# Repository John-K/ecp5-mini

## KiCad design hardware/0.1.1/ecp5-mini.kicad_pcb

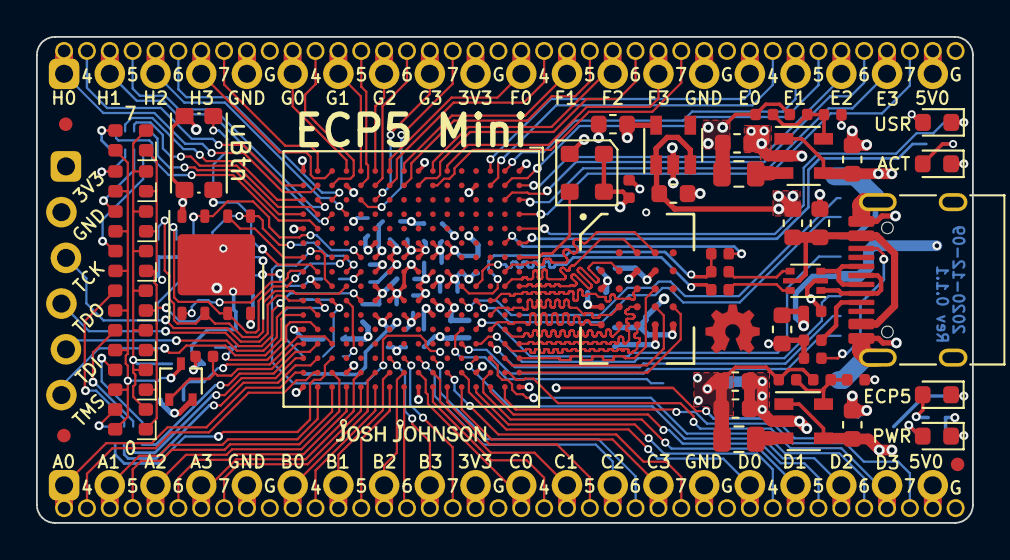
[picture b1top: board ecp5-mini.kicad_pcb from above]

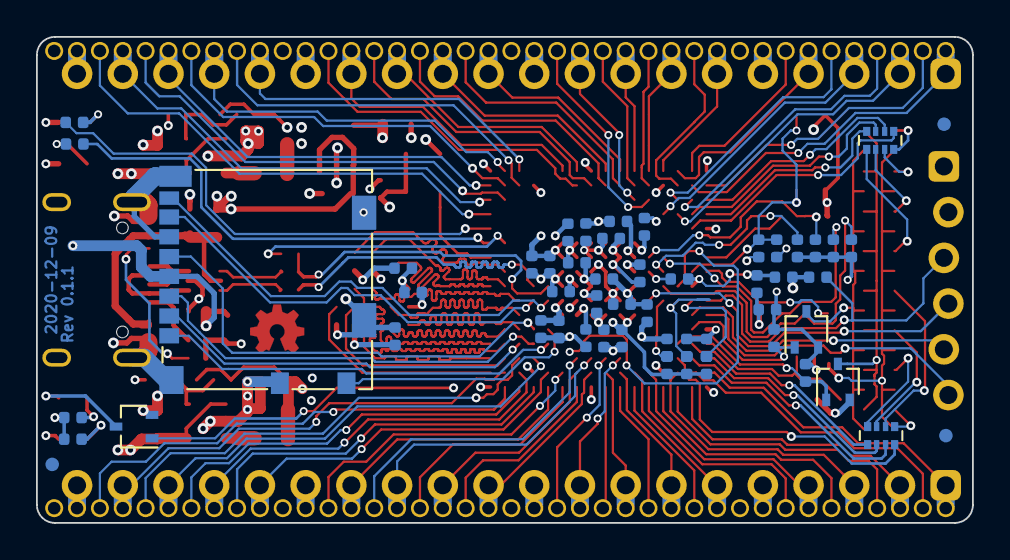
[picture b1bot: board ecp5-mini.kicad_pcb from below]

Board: 4 copper layers, 52.0 x 27.0 mm, 111 parts (55 on the bottom side), 149 nets.

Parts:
C1, C2, C6: 4u7; C_0603_1608Metric
C3, C4: 1u; C_0603_1608Metric
C5, C11: 10u; C_0603_1608Metric
C7, C10: 22u; C_0603_1608Metric
C8, C9: 6p8; C_0402_1005Metric
C12, C13, C14, C15, C17, C18, C19, C20, C25, C26, C31, C32, C37, C38, C39, C40, C41, C42, C43, C45, C46, C47: 100n; C_0402_1005Metric
C21, C22, C23, C29, C30: 4u7; C_0402_1005Metric
D1, D2, D3, D12: PINK; LED_0603_1608Metric
D4, D5, D6, D7, D8, D9, D10, D11: 2020RGBA; LED_TRI_2020
F1: 1A; Fuse_0603_1608Metric
FID1, FID2, FID3, FID4, FID5, FID6: Fiducial; Fiducial_0.75mm_Mask1.5mm
J1: Micro_SD_Card; microSD_HC_Molex_104031-0811
J2: JTAG; STM_6_PIN_THT_Staggered
J3, J4: S7 Mini; ECP5-Mini-Edge-20x2.54-40x1.27
J5: USB_C_Receptacle_USB2.0; USB_C_Receptacle_HRO_TYPE-C-31-M-12
L1, L2: 2u2; L_0805_2012Metric
LOGO1: Josh-Logo; josh-johnson-logo-8_6x1_5
LOGO2: OSHW_FMask; OSHW_Logo_3.6x3.6_F.Mask
Q1, Q2, Q3, Q4: BSS138; SOT-323_SC-70
R1: 210k; R_0402_1005Metric
R2: 47k; R_0402_1005Metric
R3: 84k5; R_0402_1005Metric
R4: 100k; R_0402_1005Metric
R5, R21, R22, R23: 2K2; R_0402_1005Metric
R6, R7, R12, R19: 5K1; R_0402_1005Metric
R8, R24, R25, R26, R27, R28, R29, R30: 10K; R_0402_1005Metric
R9, R10, R20: 22R; R_0402_1005Metric
R11, R13, R14, R15, R16, R17, R18: 1K5; R_0402_1005Metric
RN2, RN3: 220R; R_Array_Convex_4x0402
SW1: KMR2; SW_Push_KMR2
U1: ECP5U_12_CABGA256; BGA-256_14.0x14.0mm_Layout16x16_P0.8mm_Ball0.45mm_Pad0.32mm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
U2: TLV73325PDBV; SOT-23-5
U3, U5: TLV62568DBV; SOT-23-5
U4: USBLC6-2P6; SOT-666
U6: W25Q128JVPIQ; WSON-8-1EP_6x5mm_P1.27mm_EP3.4x4.3mm
U7: S27KL0641; BGA-24_5x5_6.0x8.0mm
X1: DSC6101CI2A-016; CDFN_3.2x2.5mm_XO

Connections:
+1V1: C7.1, C8.1, C10.1, C21.1, C22.1, C37.1, C39.1, C41.1, C42.1, C43.1, L2.2, R3.1, U1.G6 (VCC[6]), U1.G7 (VCC[6]), U1.G9 (VCC[6]), U1.L8 (VCC[6]), U1.L9 (VCC[6]), U1.L10 (VCC[6])
+2V5: C4.1, C38.1, C40.1, U1.G11 (VCCAUX[2]), U1.L7 (VCCAUX[2]), U2.5 (OUT)
+3V3: C5.1, C9.1, C11.1, C12.1, C14.1, C17.1, C18.1, C19.1, C20.1, C23.1, C25.1, C26.1, C29.1, C30.1, C31.1, C32.1, C45.1, C46.1, C47.1, J1.4 (VDD), J2.1, J3.19, J4.19, L1.2, R1.1, R5.1, R12.1, R13.1, R15.1, R17.1, R19.1, R21.2, R24.1, R26.1, R27.1, R29.1, U1.F6 (VCCIO0[2]), U1.F7 (VCCIO0[2]), U1.F10 (VCCIO1[2]), U1.F11 (VCCIO1[2]), U1.H6 (VCCIO7[2]), U1.H7 (VCCIO7[2]), U1.H11 (VCCIO2[2]), U1.J6 (VCCIO6[2]), U1.J7 (VCCIO6[2]), U1.J11 (VCCIO2[2]), U1.K11 (VCCIO3[2]), U1.L6 (VCCIO8), U1.L11 (VCCIO3[2]), U6.8 (VCC), U7.B4 (VCC), U7.D1 (VCCQ), U7.E4 (VCCQ), X1.1 (OE/STBY), X1.4 (VDD)
+5V: C1.1, C2.1, C3.1, F1.2, J3.39, J4.39, U2.1 (IN), U2.3 (EN), U3.1 (EN), U3.4 (VIN), U5.1 (EN), U5.4 (VIN)
/CLK_16MHZ: U1.A7 (PT29A/+/PCLKT0_0), X1.3 (OUT)
/FPGA Config/CFG_0: R13.2, R14.1, U1.N10 (CFG_0)
/FPGA Config/CFG_1: R15.2, R16.1, U1.P10 (CFG_1)
/FPGA Config/CFG_2: R17.2, R18.1, U1.R10 (CFG_2)
/FPGA Config/CFG_CDONE: Q1.1 (G), U1.P9 (DONE)
/FPGA Config/CFG_CLK: R27.2, U1.N9 (CCLK/MCLK/SCK), U6.6 (CLK)
/FPGA Config/CFG_CS: R29.2, U1.N8 (PB15A/+/HOLDN/DI/BUSY/CSSPIN/CEN), U6.1 (~CS)
/FPGA Config/CFG_IO0: U1.T8 (PB11B/-/D0/MOSI/IO0), U6.5 (DI(IO0))
/FPGA Config/CFG_IO1: U1.T7 (PB11A/+/D1/MISO/IO1), U6.2 (DO(IO1))
/FPGA Config/CFG_IO2: R26.2, U1.M7 (PB9B/-/D2/IO2), U6.3 (IO2)
/FPGA Config/CFG_IO3: R24.2, U1.N7 (PB9A/+/D3/IO3), U6.7 (IO3)
/FPGA Config/TCK: J2.3, R8.1, U1.T10 (TCK)
/FPGA Config/TDI: J2.5, U1.R11 (TDI)
/FPGA Config/TDO: J2.4, U1.M10 (TDO)
/FPGA Config/TMS: J2.6, U1.T11 (TMS)
/FPGA Config/nBTN_USR: C13.1, R12.2, SW1.2, U1.R8 (PB13A/+/SN/CSN)
/FPGA Config/nFPGA_RST: C15.1, R19.2, R20.1, U1.R9 (PROGRAMN)
/HR_CK: U1.A9 (PT42A/+), U7.B2 (CK)
/HR_DQ0: U1.A13 (PT65A/+), U7.D3 (DQ0)
/HR_DQ1: U1.C11 (PT49B/-), U7.D2 (DQ1)
/HR_DQ2: U1.A14 (PT65B/-), U7.C4 (DQ2)
/HR_DQ3: U1.B14 (PT67A/+), U7.D4 (DQ3)
/HR_DQ4: U1.A15 (PT67B/-), U7.D5 (DQ4)
/HR_DQ5: U1.B13 (PT60A/+), U7.E3 (DQ5)
/HR_DQ6: U1.B12 (PT56A/+), U7.E2 (DQ6)
/HR_DQ7: U1.C12 (PT56B/-), U7.E1 (DQ7)
/HR_RWDS: U1.C10 (PT44B/-), U7.C3 (RWDS)
/HR_nCS: U1.B9 (PT38A/+/GR_PCLK1_0), U7.A3 (~CS)
/HR_nRST: U1.B8 (PT35B/-/PCLKC1_0), U7.A4 (~RESET)
/LED_0: RN2.8, U1.P14 (PR38B/-/HS/RDQ44)
/LED_1: RN2.5, U1.R13 (PR41C/+/RDQ44)
/LED_2: RN2.6, U1.T14 (PR41D/-/RDQ44)
/LED_3: RN2.7, U1.R14 (PR41B/-/HS/RDQ44)
/LED_4: RN3.8, U1.T4 (PL44B/-/HS/LDQSN44)
/LED_5: RN3.7, U1.R4 (PL41C/+/LDQ44)
/LED_6: RN3.6, U1.T3 (PL41D/-/LDQ44)
/LED_7: RN3.5, U1.R5 (PL44A/+/HS/LDQS44)
/LED_ACT: R23.1, U1.A6 (PT18B/-)
/LED_B: Q4.1 (G), R30.1, U1.T13 (PR44B/-/HS/RDQSN44)
/LED_G: Q3.1 (G), R28.1, U1.P13 (PR41A/+/HS/RDQ44)
/LED_R: Q2.1 (G), R25.1, U1.R12 (PR44A/+/HS/RDQS44)
/LED_USR: R22.1, U1.A5 (PT18A/+)
/LEDs/CAT_B: D4.2 (BK), D5.2 (BK), D6.2 (BK), D7.2 (BK), D8.2 (BK), D9.2 (BK), D10.2 (BK), D11.2 (BK), Q4.3 (D)
/LEDs/CAT_G: D4.4 (GK), D5.4 (GK), D6.4 (GK), D7.4 (GK), D8.4 (GK), D9.4 (GK), D10.4 (GK), D11.4 (GK), Q3.3 (D)
/LEDs/CAT_R: D4.1 (RK), D5.1 (RK), D6.1 (RK), D7.1 (RK), D8.1 (RK), D9.1 (RK), D10.1 (RK), D11.1 (RK), Q2.3 (D)
/PORT_A0: J3.1, U1.T15 (PR38D/-/RDQ44)
/PORT_A1: J3.3, U1.R16 (PR35B/-/VREF1_3/HS/RDQ32)
/PORT_A2: J3.5, U1.P15 (PR32B/-/HS/RDQSN32)
/PORT_A3: J3.7, U1.M15 (PR26D/-/PCLKC3_0/RDQ32)
/PORT_A4: J3.2, U1.R15 (PR38C/+/RDQ44)
/PORT_A5: J3.4, U1.P16 (PR35A/+/HS/RDQ32)
/PORT_A6: J3.6, U1.N16 (PR32A/+/HS/RDQS32)
/PORT_A7: J3.8, U1.M16 (PR26C/+/PCLKT3_0/RDQ32)
/PORT_B0: J3.11, U1.L15 (PR26B/-/PCLKC3_1/HS/RDQ32)
/PORT_B1: J3.13, U1.K15 (PR23D/-/PCLKC2_0/RDQ20)
/PORT_B2: J3.15, U1.J15 (PR23B/-/PCLKC2_1/HS/RDQ20)
/PORT_B3: J3.17, U1.K14 (PR20D/-/RDQ20)
/PORT_B4: J3.12, U1.L16 (PR26A/+/PCLKT3_1/HS/RDQ32)
/PORT_B5: J3.14, U1.K16 (PR23C/+/PCLKT2_0/RDQ20)
/PORT_B6: J3.16, U1.J16 (PR23A/+/PCLKT2_1/HS/RDQ20)
/PORT_B7: J3.18, U1.J14 (PR20C/+/GR_PCLK2_0/RDQ20)
/PORT_C0: J3.21, U1.H15 (PR20B/-/HS/RDQSN20)
/PORT_C1: J3.23, U1.G15 (PR14B/-/HS/RDQ20)
/PORT_C2: J3.25, U1.H14 (PR14D/-/RDQ20)
/PORT_C3: J3.27, U1.E16 (PR11D/-/RDQ8)
/PORT_C4: J3.22, U1.G16 (PR20A/+/GR_PCLK2_1/HS/RDQS20)
/PORT_C5: J3.24, U1.F16 (PR14A/+/HS/RDQ20)
/PORT_C6: J3.26, U1.G14 (PR14C/+/VREF1_2/RDQ20)
/PORT_C7: J3.28, U1.F15 (PR11C/+/RDQ8)
/PORT_D0: J3.31, U1.E15 (PR8B/-/HS/RDQSN8)
/PORT_D1: J3.33, U1.C15 (PR5B/-/HS/RDQ8)
/PORT_D2: J3.35, U1.D14 (PR2D/-/RDQ8)
/PORT_D3: J3.37, U1.B15 (PR2B/-/S0_IN/HS/RDQ8)
/PORT_D4: J3.32, U1.D16 (PR8A/+/HS/RDQS8)
/PORT_D5: J3.34, U1.C16 (PR5A/+/HS/RDQ8)
/PORT_D6: J3.36, U1.C14 (PR2C/+/RDQ8)
/PORT_D7: J3.38, U1.B16 (PR2A/+/HS/RDQ8)
/PORT_E0: J4.31, U1.C1 (PL5A/+/HS/LDQ8)
/PORT_E1: J4.33, U1.B1 (PL2A/+/HS/LDQ8)
/PORT_E2: J4.35, U1.A2 (PT4A/+)
/PORT_E3: J4.37, U1.A3 (PT6A/+)
/PORT_E4: J4.32, U1.C2 (PL5B/-/HS/LDQ8)
/PORT_E5: J4.34, U1.B2 (PL2B/-/HS/LDQ8)
/PORT_E6: J4.36, U1.B3 (PT4B/-)
/PORT_E7: J4.38, U1.A4 (PT6B/-)
/PORT_F0: J4.21, U1.K1 (PL23C/+/PCLKT7_0/LDQ20)
/PORT_F1: J4.23, U1.J1 (PL23A/+/PCLKT7_1/HS/LDQ20)
/PORT_F2: J4.25, U1.G1 (PL20A/+/GR_PCLK7_1/HS/LDQS20)
/PORT_F3: J4.27, U1.F1 (PL14A/+/HS/LDQ20)
/PORT_F4: J4.22, U1.K2 (PL23D/-/PCLKC7_0/LDQ20)
/PORT_F5: J4.24, U1.J2 (PL23B/-/PCLKC7_1/HS/LDQ20)
/PORT_F6: J4.26, U1.H2 (PL20B/-/HS/LDQSN20)
/PORT_F7: J4.28, U1.G2 (PL14B/-/HS/LDQ20)
/PORT_G0: J4.11, U1.N1 (PL32A/+/HS/LDQS32)
/PORT_G1: J4.13, U1.M1 (PL26C/+/PCLKT6_0/LDQ32)
/PORT_G2: J4.15, U1.L1 (PL26A/+/PCLKT6_1/HS/LDQ32)
/PORT_G3: J4.17, U1.L3 (PL32C/+/LDQ32)
/PORT_G4: J4.12, U1.P2 (PL32B/-/HS/LDQSN32)
/PORT_G5: J4.14, U1.M2 (PL26D/-/PCLKC6_0/LDQ32)
/PORT_G6: J4.16, U1.L2 (PL26B/-/PCLKC6_1/HS/LDQ32)
/PORT_G7: J4.18, U1.M3 (PL32D/-/LDQ32)
/PORT_H0: J4.1, U1.R2 (PL38C/+/LDQ44)
/PORT_H1: J4.3, U1.P4 (PL41A/+/HS/LDQ44)
/PORT_H2: J4.5, U1.N4 (PL38A/+/HS/LDQ44)
/PORT_H3: J4.7, U1.P1 (PL35A/+/HS/LDQ32)
/PORT_H4: J4.2, U1.T2 (PL38D/-/LDQ44)
/PORT_H5: J4.4, U1.R3 (PL41B/-/HS/LDQ44)
/PORT_H6: J4.6, U1.P3 (PL38B/-/HS/LDQ44)
/PORT_H7: J4.8, U1.R1 (PL35B/-/VREF1_6/HS/LDQ32)
/SD_CLK: J1.5 (CLK), U1.D12 (PT58A/+)
/SD_CMD: J1.3 (CMD), U1.D13 (PT62A/+)
/SD_DAT0: J1.7 (DAT0), U1.D10 (PT47A/+)
/SD_DAT1: J1.8 (DAT1), U1.E10 (PT47B/-)
/SD_DAT2: J1.1 (DAT2), U1.E13 (PT62B/-)
/SD_DAT3: J1.2 (DAT3/CD), U1.C13 (PT60B/-)
/SD_DET: J1.10 (DET_A), U1.E12 (PT58B/-)
/USB_D+: R10.1, R11.1, U1.E9 (PT40B/-)
/USB_D-: R9.2, U1.D9 (PT40A/+)
/USB_PU: R11.2, U1.B6 (PT22B/-)
GND: C1.2, C2.2, C3.2, C4.2, C5.2, C6.2, C7.2, C10.2, C11.2, C12.2, C13.2, C14.2, C15.2, C17.2, C18.2, C19.2, C20.2, C21.2, C22.2, C23.2, C25.2, C26.2, C29.2, C30.2, C31.2, C32.2, C37.2, C38.2, C39.2, C40.2, C41.2, C42.2, C43.2, C45.2, C46.2, C47.2, D1.1 (K), D3.1 (K), D12.1 (K), J1.6 (VSS), J1.9 (DET_B), J1.11 (SHIELD), J2.2, J3.9, J3.10, J3.20, J3.29, J3.30, J3.40, J4.9, J4.10, J4.20, J4.29, J4.30, J4.40, J5.A1 (GND), J5.A12 (GND), J5.B1 (GND), J5.B12 (GND), J5.S1 (SHIELD), Q1.2 (S), Q2.2 (S), Q3.2 (S), Q4.2 (S), R2.2, R4.2, R6.2, R7.2, R8.2, R14.2, R16.2, R18.2, R25.2, R28.2, R30.2, SW1.1, U1.A1 (GND[27]), U1.A16 (GND[27]), U1.D2 (GND[27]), U1.D15 (GND[27]), U1.F8 (GND[27]), U1.F9 (GND[27]), U1.G8 (GND[27]), U1.G10 (GND[27]), U1.H1 (GND[27]), U1.H8 (GND[27]), U1.H9 (GND[27]), U1.H10 (GND[27]), U1.H16 (GND[27]), U1.J8 (GND[27]), U1.J9 (GND[27]), U1.J10 (GND[27]), U1.K6 (GND[27]), U1.K7 (GND[27]), U1.K8 (GND[27]), U1.K9 (GND[27]), U1.K10 (GND[27]), U1.N2 (GND[27]), U1.N15 (GND[27]), U1.T1 (GND[27]), U1.T5 (GND[27]), U1.T12 (GND[27]), U1.T16 (GND[27]), U2.2 (GND), U3.2 (GND), U4.2 (GND), U5.2 (GND), U6.4 (GND), U6.9 (GND), U7.B3 (VSS), U7.C1 (VSSQ), U7.E5 (VSSQ), X1.2 (GND)
unnamed: C6.1, F1.1, J5.A4 (VBUS), J5.A9 (VBUS), J5.B4 (VBUS), J5.B9 (VBUS), U4.5 (VBUS)
unnamed: C8.2, R3.2, R4.1, U5.5 (FB)
unnamed: C9.2, R1.2, R2.1, U3.5 (FB)
unnamed: D1.2 (A), R5.2
unnamed: D2.1 (K), Q1.3 (D)
unnamed: D2.2 (A), R21.1
unnamed: D3.2 (A), R22.2
unnamed: D4.3 (A), RN2.1
unnamed: D5.3 (A), RN2.4
unnamed: D6.3 (A), RN2.3
unnamed: D7.3 (A), RN2.2
unnamed: D8.3 (A), RN3.1
unnamed: D9.3 (A), RN3.2
unnamed: D10.3 (A), RN3.3
unnamed: D11.3 (A), RN3.4
unnamed: D12.2 (A), R23.2
unnamed: J5.A5 (CC1), R6.1
unnamed: J5.A6 (D+), J5.B6 (D+), U4.3 (IO2)
unnamed: J5.A7 (D-), J5.B7 (D-), U4.1 (IO1)
unnamed: J5.B5 (CC2), R7.1
unnamed: L1.1, U3.3 (SW)
unnamed: L2.1, U5.3 (SW)
unnamed: R9.1, U4.6 (IO1)
unnamed: R10.2, U4.4 (IO2)
unnamed: R20.2, U1.M8 (PB15B/-/DOUT/CSON)

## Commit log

2020-12-09 Resolve T12 via issue and feng-shui some traces
2020-12-09 Update board date and version
